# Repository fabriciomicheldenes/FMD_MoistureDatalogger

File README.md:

# 🌱 Datalogger de Umidade do Solo *FMD_Soil Moisture*

## 📘 Visão Geral

 O **FMD_Soil Moisture** é um sistema autônomo para **monitoramento contínuo de umidade e temperatura do solo**, com armazenamento local e conectividade Wi-Fi e Serial-USB.

Projetado para aplicações agrícolas e experimentais, o sistema registra dados ambientais em longo prazo com alta confiabilidade e baixo custo.

O projeto é baseado em um **Arduino Mega 2560**, que coleta leituras de múltiplos sensores capacitivos de umidade do solo **HW-101 HW**, além de um sensor **DHT22** para temperatura e umidade do ar.

Os dados são registrados em **cartão microSD** e podem ser sincronizados via **módulo ESP-01 (ESP8266)** para monitoramento remoto.

## 🧩 Hardware - Arquitetura Geral

### 🔹 Componentes Principais

| Módulo / Componente                                         | Função                            | Interface         | Observações                                                        |
| ----------------------------------------------------------- | --------------------------------- | ----------------- | ------------------------------------------------------------------ |
| **Arduino Mega 2560**                                       | Unidade de controle principal     | –                 | 16 canais analógicos nativos + expansão SPI                        |
| **Sensores de Umidade Capacitivos (HW-101 HW V1.2 / V2.0)** | Medição de umidade do solo        | Analógica (0–5 V) | 16 sensores diretos + 2 via MCP3008                                |
| **MCP3008**                                                 | Conversor A/D externo de 8 canais | SPI               | Expande entradas                                                   |
| **DHT22**                                                   | Temperatura e umidade do ar       | 1 fio (digital)   | Sensor ambiente                                                    |
| **ESP-01 (ESP8266)**                                        | Comunicação Wi-Fi                 | UART              | Upload de dados ou configuração remota                             |
| **RTC DS1307 + Bateria 3 V**                                | Relógio e calendário              | I²C               | Mantém data/hora durante desligamento                              |
| **MicroSD Card (SPI)**                                      | Armazenamento local               | SPI               | Indicadores de status via LEDs                                     |
| **LEDs de Status (3×)**                                     | Indicação do estado do SDCard     | GPIO              | - Sem cartão<br>- Falha no cartão<br>- Cartão OK (pisca ao gravar) |

## ⚙️ Recursos Adicionais (não implementados (no firmware) na versão atual)

| Recurso                | Componente              | Interface | Estado    |
| ---------------------- | ----------------------- | --------- | --------- |
| Memória EEPROM externa | 24C32WP                 | I²C       | Reservado |
| Display LCD 1602       | HD44780 (modo 4 bits)   | GPIO      | Reservado |
| Display 5110           | Nokia 5110              | SPI       | Reservado |
| Teclado                | Teclado matricial 4×4   | GPIO      | Reservado |
| Expansão ADC           | MCP3008 (canais livres) | SPI       | Reservado |

## 🔌 Conectores de Expansão

| Conector                | Interface               | Descrição                                          |
| ----------------------- | ----------------------- | -------------------------------------------------- |
| **Expansão A**          | I²C, 1× I/O, 2× PWM     | Compatível com sensores e atuadores externos       |
| **Expansão B**          | SPI, CS, 1× I/O, 1× PWM | Para módulos SPI adicionais                        |
| **Expansão C**          | SPI, CS, 1× I/O, 1× PWM | Similar à Expansão B                               |
| **Expansão D (Serial)** | TX/RX, 1× I/O, 2× PWM   | Conexão de módulos seriais ou periféricos externos |
| **Planejado**           | RS-232 e RS-485         | UART + controle de hardware                        |

## 🧾 Histórico de Versões do Hardware

| Versão   | Plataforma            | Descrição                                               | Status    |
| -------- | --------------------- | ------------------------------------------------------- | --------- |
| **V0.1** | Proteus (ISIS + ARES) | Primeira versão funcional do circuito e layout          | ✅ Testada |
| **V0.2** | KiCad 8               | Novo layout, roteamento otimizado e serigrafia revisada | 🔄 Atual  |

A **versão V0.1**, desenvolvida no *Proteus (ISIS + ARES)*, foi a primeira versão funcional do hardware, mas apresentava algumas limitações de projeto, como trilhas longas e cruzadas, componentes em ambos os lados e uso reduzido de plano de terra, exigindo pequenas correções com jumpers.

A **versão V0.2**, redesenhada no *KiCad 8*, manteve o mesmo circuito eletrônico, mas trouxe um layout mais maduro e eficiente: todos os componentes estão em um único lado, as trilhas são curtas e bem distribuídas, e há ampla costura de planos de terra em ambas as faces, resultando em **melhor imunidade a ruídos** e maior confiabilidade do sistema.

## 💾 Firmware

O firmware foi desenvolvido em **Arduino C++**, com foco em modularidade e confiabilidade para operação contínua.  
Ele realiza:

- Leitura sequencial dos sensores de umidade e do DHT22  
- Registro no **RTC DS1307** para carimbo de data/hora  
- Armazenamento no **microSD (FAT32)**  
- Indicação visual do status via LEDs  
- Envio de dados via **Wi-Fi (ESP-01)**  

### 🔹 Bibliotecas utilizadas

- `DHT.h` – leitura de temperatura/umidade  
- `Wire.h` – comunicação I²C (RTC e EEPROM)  
- `SPI.h` – comunicação SPI (SD e MCP3008)  
- `SD.h` – gerenciamento do cartão microSD  
- `SoftwareSerial.h` – interface serial com ESP-01  

> 🔗 Detalhes do código e pinagem em [`Firmware/README.md`](Firmware/README.md)

---

## 💻 Software de Visualização

O software de visualização foi desenvolvido em **Python/Qt**, permitindo:

- Leitura direta dos arquivos `.CSV` ou `.TXT` do microSD  
- Exibição de gráficos de tendência (umidade x tempo)  
- Exportação dos dados para análise estatística  
- Modo de operação **offline (SD)** e **online (Wi-Fi)**  

> 🔗 Documentação completa em [`Software/README.md`](Software/README.md)

---

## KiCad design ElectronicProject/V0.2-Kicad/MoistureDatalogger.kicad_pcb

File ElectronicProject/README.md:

# 🌱 Datalogger de Umidade do Solo *FMD_Soil Moisture* – Hardware

## 📘 Visão Geral

 O **FMD_Soil Moisture** é um sistema autônomo para **monitoramento contínuo de umidade e temperatura do solo**, com armazenamento local e conectividade Wi-Fi e Serial-USB.

Projetado para aplicações agrícolas e experimentais, o sistema registra dados ambientais em longo prazo com alta confiabilidade e baixo custo.

O projeto é baseado em um **Arduino Mega 2560**, que coleta leituras de múltiplos sensores capacitivos de umidade do solo **HW-101 HW**, além de um sensor **DHT22** para temperatura e umidade do ar.

Os dados são registrados em **cartão microSD** e podem ser sincronizados via **módulo ESP-01 (ESP8266)** para monitoramento remoto.

## 🧩 Arquitetura Geral

### 🔹 Componentes Principais

| Módulo / Componente                                         | Função                            | Interface         | Observações                                                        |
| ----------------------------------------------------------- | --------------------------------- | ----------------- | ------------------------------------------------------------------ |
| **Arduino Mega 2560**                                       | Unidade de controle principal     | –                 | 16 canais analógicos nativos + expansão SPI                        |
| **Sensores de Umidade Capacitivos (HW-101 HW V1.2 / V2.0)** | Medição de umidade do solo        | Analógica (0–5 V) | 16 sensores diretos + 2 via MCP3008                                |
| **MCP3008**                                                 | Conversor A/D externo de 8 canais | SPI               | Expande entradas                                                   |
| **DHT22**                                                   | Temperatura e umidade do ar       | 1 fio (digital)   | Sensor ambiente                                                    |
| **ESP-01 (ESP8266)**                                        | Comunicação Wi-Fi                 | UART              | Upload de dados ou configuração remota                             |
| **RTC DS1307 + Bateria 3 V**                                | Relógio e calendário              | I²C               | Mantém data/hora durante desligamento                              |
| **MicroSD Card (SPI)**                                      | Armazenamento local               | SPI               | Indicadores de status via LEDs                                     |
| **LEDs de Status (3×)**                                     | Indicação do estado do SDCard     | GPIO              | - Sem cartão<br>- Falha no cartão<br>- Cartão OK (pisca ao gravar) |

## ⚙️ Recursos Adicionais (não implementados (no firmware) na versão atual)

| Recurso                | Componente              | Interface | Estado    |
| ---------------------- | ----------------------- | --------- | --------- |
| Memória EEPROM externa | 24C32WP                 | I²C       | Reservado |
| Display LCD 1602       | HD44780 (modo 4 bits)   | GPIO      | Reservado |
| Display 5110           | Nokia 5110              | SPI       | Reservado |
| Teclado                | Teclado matricial 4×4   | GPIO      | Reservado |
| Expansão ADC           | MCP3008 (canais livres) | SPI       | Reservado |

## 🔌 Conectores de Expansão

| Conector                | Interface               | Descrição                                          |
| ----------------------- | ----------------------- | -------------------------------------------------- |
| **Expansão A**          | I²C, 1× I/O, 2× PWM     | Compatível com sensores e atuadores externos       |
| **Expansão B**          | SPI, CS, 1× I/O, 1× PWM | Para módulos SPI adicionais                        |
| **Expansão C**          | SPI, CS, 1× I/O, 1× PWM | Similar à Expansão B                               |
| **Expansão D (Serial)** | TX/RX, 1× I/O, 2× PWM   | Conexão de módulos seriais ou periféricos externos |
| **Planejado**           | RS-232 e RS-485         | UART + controle de hardware                        |

## 🧾 Histórico de Versões do Hardware

| Versão   | Plataforma            | Descrição                                               | Status    |
| -------- | --------------------- | ------------------------------------------------------- | --------- |
| **V0.1** | Proteus (ISIS + ARES) | Primeira versão funcional do circuito e layout          | ✅ Testada |
| **V0.2** | KiCad 8               | Novo layout, roteamento otimizado e serigrafia revisada | 🔄 Atual  |

As **Figuras 1 e 2** apresentam a **versão V0.1** da placa, elaborada utilizando o *Proteus* (ISIS + ARES).  
Embora plenamente funcional, essa versão apresentou algumas limitações construtivas, como **trilhas incompletas que precisaram ser interligadas externamente por jumpers**, um **layout ainda imaturo** com **componentes montados em ambos os lados da placa** e **trilhas longas que se cruzam**, resultando em **pouca área disponível para o plano de terra**.  
Esses aspectos podem ser observados nas **Figuras 3 e 4**, que mostram os lados **superior** e **inferior** da placa.

<figure>
  
  <figcaption align="center"><b>Figura 1</b>: Placa V0.1 vista de cima.  <b> Figura 2</b>: – Placa V0.1 vista de baixo.</figcaption>
</figure>

<figure>
  
  <figcaption align="center"><b>Figura 3</b>: Placa V0.1 Top layer.  <b> Figura 4</b>: – Placa V0.1 Bottom layer.</figcaption>
</figure>>

A **versão V0.2**, desenvolvida no **KiCad**, manteve o mesmo circuito eletrônico da versão anterior, porém recebeu um **layout totalmente refeito**, com foco em otimização e robustez.  
Como ilustrado nas **Figuras 5 e 6**, o novo modelo 3D demonstra um **posicionamento mais racional dos componentes**, concentrados **em um único lado da placa**, com **trilhas mais curtas e diretas** e **ampla área para planos de terra em ambas as faces**.  
As **Figuras 7 e 8** evidenciam também a **costura entre planos de terra**, que contribui para **melhorar a imunidade a ruídos** e **reduzir interferências eletromagnéticas (EMI)**, tornando o hardware mais confiável para uso em ambientes agrícolas sujeitos a variações de umidade e ruído elétrico.

<figure>
  
  <figcaption align="center"><b>Figura 5</b>: Placa V0.2 vista de cima, modelo 3D.  <b> Figura 6</b>: – Placa V0.2 vista de baixo, modelo 3D.</figcaption>
</figure>

<figure>
  
  <figcaption align="center"><b>Figura 7</b>: Placa V0.2 Top layer.  <b> Figura 8</b>: – Placa V0.2 Bottom layer.</figcaption>
</figure>>

## 🧮 Especificações Técnicas

- **Alimentação:** 7 – 12 V DC
- **Consumo típico:** ~200 mA (sem Wi-Fi ativo)
- **Número total de canais de umidade:** 18
- **Resolução ADC (interna):** 10 bits
- **Resolução ADC (externa):** 10 bits (MCP3008)
- **Período de amostragem:** configurável (ex.: 5 s a 10 min)
- **Armazenamento:** microSD FAT32 (até 32 GB)
- **Conectividade:** Wi-Fi (ESP-01), Serial USB

## 🧰 Próximas Melhorias

- Implementação do barramento **RS-485** para rede de sensores.
- Inclusão de **display LCD/Nokia** para feedback local.
- Sistema de **menus via teclado matricial**.
- Adição de **EEPROM 24C32WP** para parâmetros persistentes.

## 📁 Estrutura de Pastas (Hardware)

## 📜 Licença

Este projeto é distribuído sob a licença **MIT**, permitindo uso, modificação e distribuição com atribuição ao autor.

---

**Autor:** Fabrício Michel Denes  
**Repositório:** [github.com/fabriciomicheldenes/FMD_MoistureDatalogger](https://github.com/fabriciomicheldenes/FMD_MoistureDatalogger)

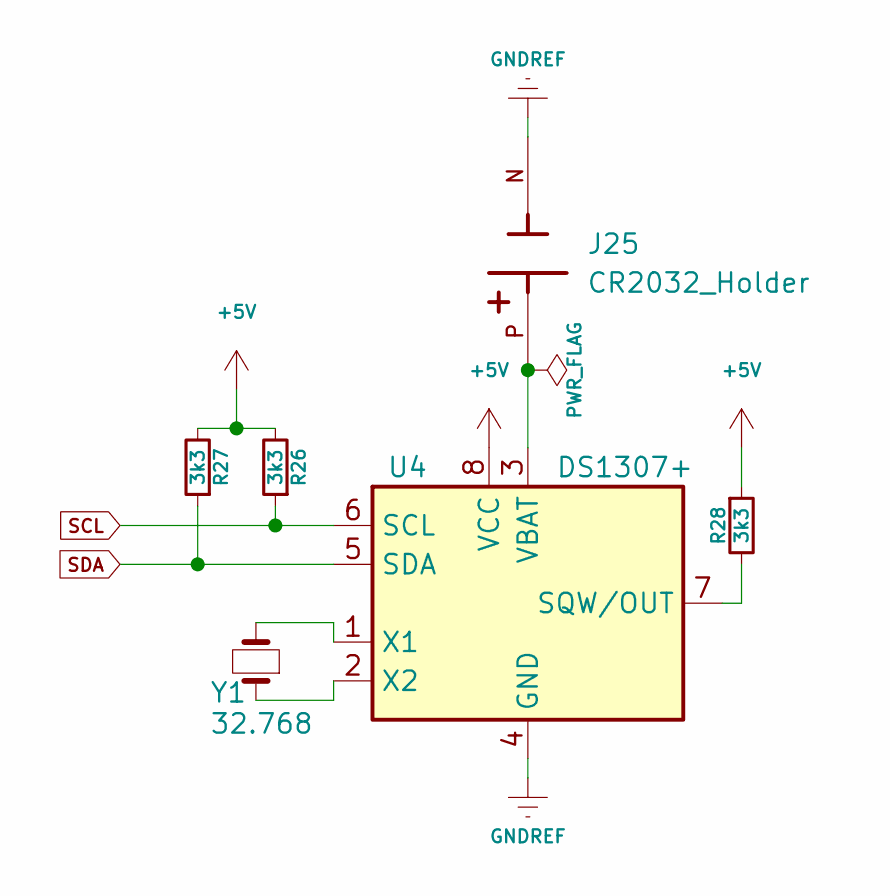
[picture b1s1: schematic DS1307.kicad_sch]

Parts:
J25: CR2032_Holder; HARWIN_S8421-45R
R26, R27, R28: 3k3; R_0805_2012Metric
U4: DS1307+; SOIC-8_3.9x4.9mm_P1.27mm
Y1: 32.768; Crystal_DS26_D2.0mm_L6.0mm_Vertical

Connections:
+5V: R26.2, R27.2, R28.1, U4.8 (VCC); also elsewhere on the board
GNDREF: J25.N, U4.4 (GND); also elsewhere on the board
unnamed: R28.2, U4.7 (SQW/OUT)
unnamed: J25.P, U4.3 (VBAT)
unnamed: U4.1 (X1), Y1.2
unnamed: U4.2 (X2), Y1.1
SCL: R26.1, U4.6 (SCL); also elsewhere on the board
SDA: R27.1, U4.5 (SDA); also elsewhere on the board

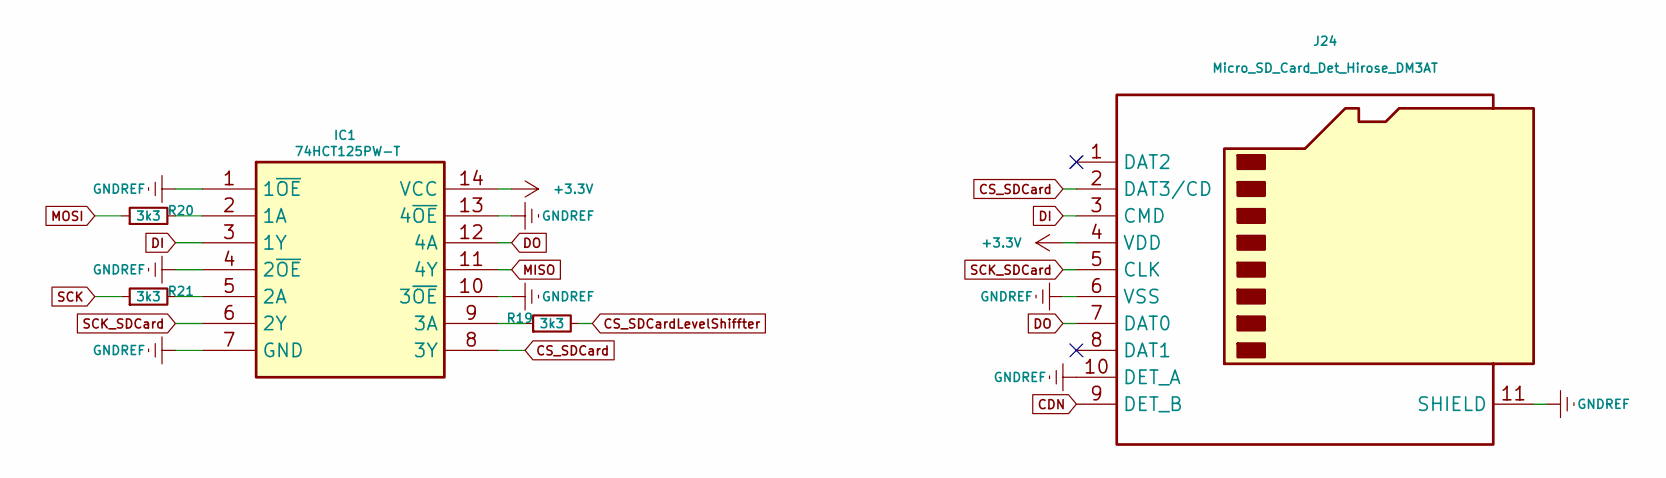
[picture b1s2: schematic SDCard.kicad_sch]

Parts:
IC1: 74HCT125PW-T; SOIC-14_3.9x8.7mm_P1.27mm; Manufacturer_Part_Number 74HCT125PW-T
J24: Micro_SD_Card_Det_Hirose_DM3AT; microSD_HC_Hirose_DM3AT-SF-PEJM5
R19, R20, R21: 3k3; R_0805_2012Metric

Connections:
+3.3V: IC1.14 (VCC), J24.4 (VDD); also elsewhere on the board
CDN: J24.9 (DET_B); also elsewhere on the board
CS_SDCard: IC1.8 (3Y), J24.2 (DAT3/CD)
CS_SDCardLevelShiffter: R19.2; also elsewhere on the board
DI: IC1.3 (1Y), J24.3 (CMD)
DO: IC1.12 (4A), J24.7 (DAT0)
GNDREF: IC1.1 (1~OE), IC1.4 (2~OE), IC1.7 (GND), IC1.10 (3~OE), IC1.13 (4~OE), J24.6 (VSS), J24.10 (DET_A), J24.11 (SHIELD); also elsewhere on the board
MISO: IC1.11 (4Y); also elsewhere on the board
MOSI: R20.1; also elsewhere on the board
unnamed: IC1.2 (1A), R20.2
unnamed: IC1.5 (2A), R21.2
unnamed: IC1.9 (3A), R19.1
SCK: R21.1; also elsewhere on the board
SCK_SDCard: IC1.6 (2Y), J24.5 (CLK)

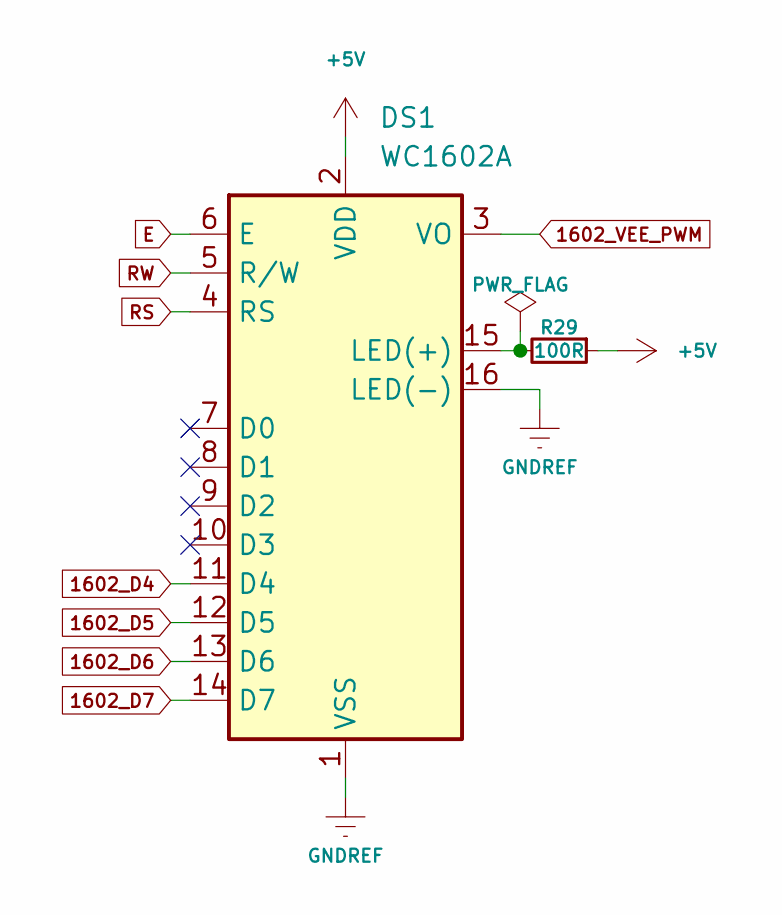
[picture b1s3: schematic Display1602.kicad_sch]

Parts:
DS1: WC1602A; JST_XH_B16B-XH-A_1x16_P2.50mm_Vertical
R29: 100R; R_0805_2012Metric

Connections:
1602_D4: DS1.11 (D4); also elsewhere on the board
1602_D5: DS1.12 (D5); also elsewhere on the board
1602_D6: DS1.13 (D6); also elsewhere on the board
1602_D7: DS1.14 (D7); also elsewhere on the board
1602_VEE_PWM: DS1.3 (VO); also elsewhere on the board
+5V: DS1.2 (VDD), R29.1; also elsewhere on the board
E: DS1.6 (E); also elsewhere on the board
GNDREF: DS1.1 (VSS), DS1.16 (LED(-)); also elsewhere on the board
unnamed: DS1.15 (LED(+)), R29.2
RS: DS1.4 (RS); also elsewhere on the board
RW: DS1.5 (R/W); also elsewhere on the board

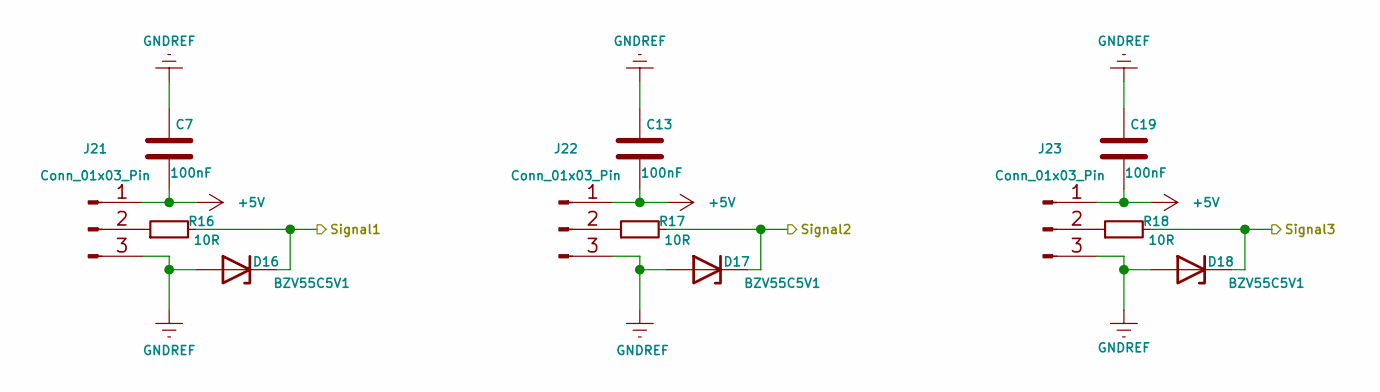
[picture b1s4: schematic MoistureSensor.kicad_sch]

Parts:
C7, C13, C19: 100nF; C_0805_2012Metric
D16, D17, D18: BZV55C5V1; D_DO-15_P10.16mm_Horizontal
J21, J22, J23: Conn_01x03_Pin; JST_XH_B3B-XH-AM_1x03_P2.50mm_Vertical
R16, R17, R18: 10R; R_0805_2012Metric

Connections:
+5V: C7.2, C13.2, C19.2, J21.1, J22.1, J23.1; also elsewhere on the board
/Microcontroller2560/A0: D16.1 (K), R16.2; also elsewhere on the board
/Microcontroller2560/A1: D17.1 (K), R17.2; also elsewhere on the board
/Microcontroller2560/A2: D18.1 (K), R18.2; also elsewhere on the board
GNDREF: C7.1, C13.1, C19.1, D16.2 (A), D17.2 (A), D18.2 (A), J21.3, J22.3, J23.3; also elsewhere on the board
unnamed: J21.2, R16.1
unnamed: J22.2, R17.1
unnamed: J23.2, R18.1

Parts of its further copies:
C8, C9, C10, C11, C12, C14, C15, C16, C17, C18, C20, C21, C22, C23, C24: 100nF; C_0805_2012Metric
D1, D2, D3, D4, D5, D6, D7, D8, D9, D10, D11, D12, D13, D14, D15: BZV55C5V1; D_DO-15_P10.16mm_Horizontal
J5, J6, J7, J8, J9, J10, J11, J12, J13, J14, J15, J16, J17, J18, J19: Conn_01x03_Pin; JST_XH_B3B-XH-AM_1x03_P2.50mm_Vertical
R1, R2, R3, R4, R5, R6, R7, R8, R9, R10, R11, R12, R13, R14, R15: 10R; R_0805_2012Metric

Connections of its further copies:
+5V: C8.2, C9.2, C10.2, C11.2, C12.2, C14.2, C15.2, C16.2, C17.2, C18.2, C20.2, C21.2, C22.2, C23.2, C24.2, J5.1, J6.1, J7.1, J8.1, J9.1, J10.1, J11.1, J12.1, J13.1, J14.1, J15.1, J16.1, J17.1, J18.1, J19.1; also elsewhere on the board
/MCP3008/A16: D14.1 (K), R14.2; also elsewhere on the board
/MCP3008/A17: D15.1 (K), R15.2; also elsewhere on the board
/Microcontroller2560/A3: D1.1 (K), R1.2; also elsewhere on the board
/Microcontroller2560/A4: D2.1 (K), R2.2; also elsewhere on the board
/Microcontroller2560/A5: D3.1 (K), R3.2; also elsewhere on the board
/Microcontroller2560/A6: D4.1 (K), R4.2; also elsewhere on the board
/Microcontroller2560/A7: D5.1 (K), R5.2; also elsewhere on the board
/Microcontroller2560/A8: D6.1 (K), R6.2; also elsewhere on the board
/Microcontroller2560/A9: D7.1 (K), R7.2; also elsewhere on the board
/Microcontroller2560/A10: D8.1 (K), R8.2; also elsewhere on the board
/Microcontroller2560/A11: D9.1 (K), R9.2; also elsewhere on the board
/Microcontroller2560/A12: D10.1 (K), R10.2; also elsewhere on the board
/Microcontroller2560/A13: D11.1 (K), R11.2; also elsewhere on the board
/Microcontroller2560/A14: D12.1 (K), R12.2; also elsewhere on the board
/Microcontroller2560/A15: D13.1 (K), R13.2; also elsewhere on the board
GNDREF: C8.1, C9.1, C10.1, C11.1, C12.1, C14.1, C15.1, C16.1, C17.1, C18.1, C20.1, C21.1, C22.1, C23.1, C24.1, D1.2 (A), D2.2 (A), D3.2 (A), D4.2 (A), D5.2 (A), D6.2 (A), D7.2 (A), D8.2 (A), D9.2 (A), D10.2 (A), D11.2 (A), D12.2 (A), D13.2 (A), D14.2 (A), D15.2 (A), J5.3, J6.3, J7.3, J8.3, J9.3, J10.3, J11.3, J12.3, J13.3, J14.3, J15.3, J16.3, J17.3, J18.3, J19.3; also elsewhere on the board
unnamed: J5.2, R1.1
unnamed: J6.2, R2.1
unnamed: J7.2, R3.1
unnamed: J8.2, R4.1
unnamed: J9.2, R5.1
unnamed: J10.2, R6.1
unnamed: J11.2, R7.1
unnamed: J12.2, R8.1
unnamed: J13.2, R9.1
unnamed: J14.2, R10.1
unnamed: J15.2, R11.1
unnamed: J16.2, R12.1
unnamed: J17.2, R13.1
unnamed: J18.2, R14.1
unnamed: J19.2, R15.1

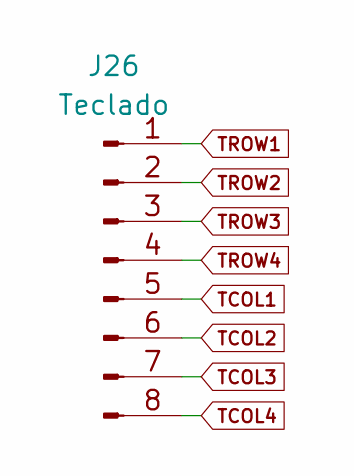
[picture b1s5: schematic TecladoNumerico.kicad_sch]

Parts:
J26: Teclado; JST_XH_B8B-XH-A_1x08_P2.50mm_Vertical

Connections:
TCOL1: J26.5; also elsewhere on the board
TCOL2: J26.6; also elsewhere on the board
TCOL3: J26.7; also elsewhere on the board
TCOL4: J26.8; also elsewhere on the board
TROW1: J26.1; also elsewhere on the board
TROW2: J26.2; also elsewhere on the board
TROW3: J26.3; also elsewhere on the board
TROW4: J26.4; also elsewhere on the board

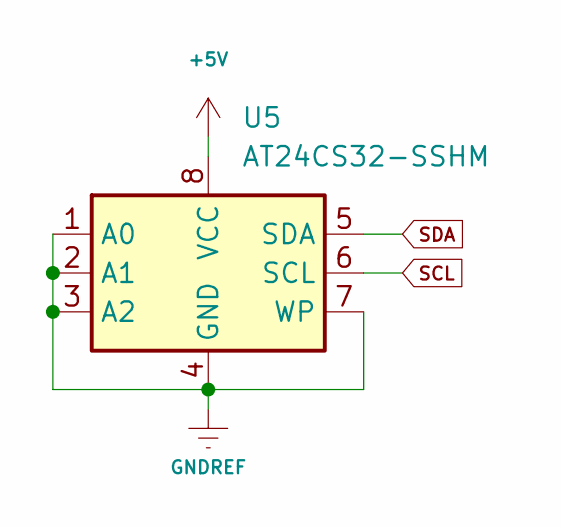
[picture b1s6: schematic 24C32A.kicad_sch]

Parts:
U5: AT24CS32-SSHM; SOIC-8_3.9x4.9mm_P1.27mm

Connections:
+5V: U5.8 (VCC); also elsewhere on the board
GNDREF: U5.1 (A0), U5.2 (A1), U5.3 (A2), U5.4 (GND), U5.7 (WP); also elsewhere on the board
SCL: U5.6 (SCL); also elsewhere on the board
SDA: U5.5 (SDA); also elsewhere on the board

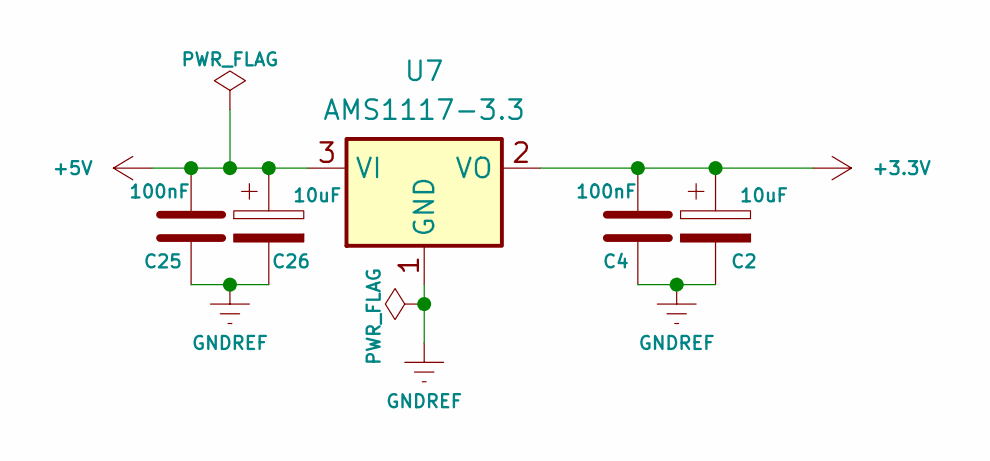
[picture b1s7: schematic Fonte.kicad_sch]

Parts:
C2: 10uF; C_0805_2012Metric
C4, C25: 100nF; C_0805_2012Metric
C26: 10uF; CP_Elec_5x5.8
U7: AMS1117-3.3; SOT-223-3_TabPin2

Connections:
+3.3V: C2.1, C4.2, U7.2 (VO); also elsewhere on the board
+5V: C25.2, C26.1, U7.3 (VI); also elsewhere on the board
GNDREF: C2.2, C4.1, C25.1, C26.2, U7.1 (GND); also elsewhere on the board

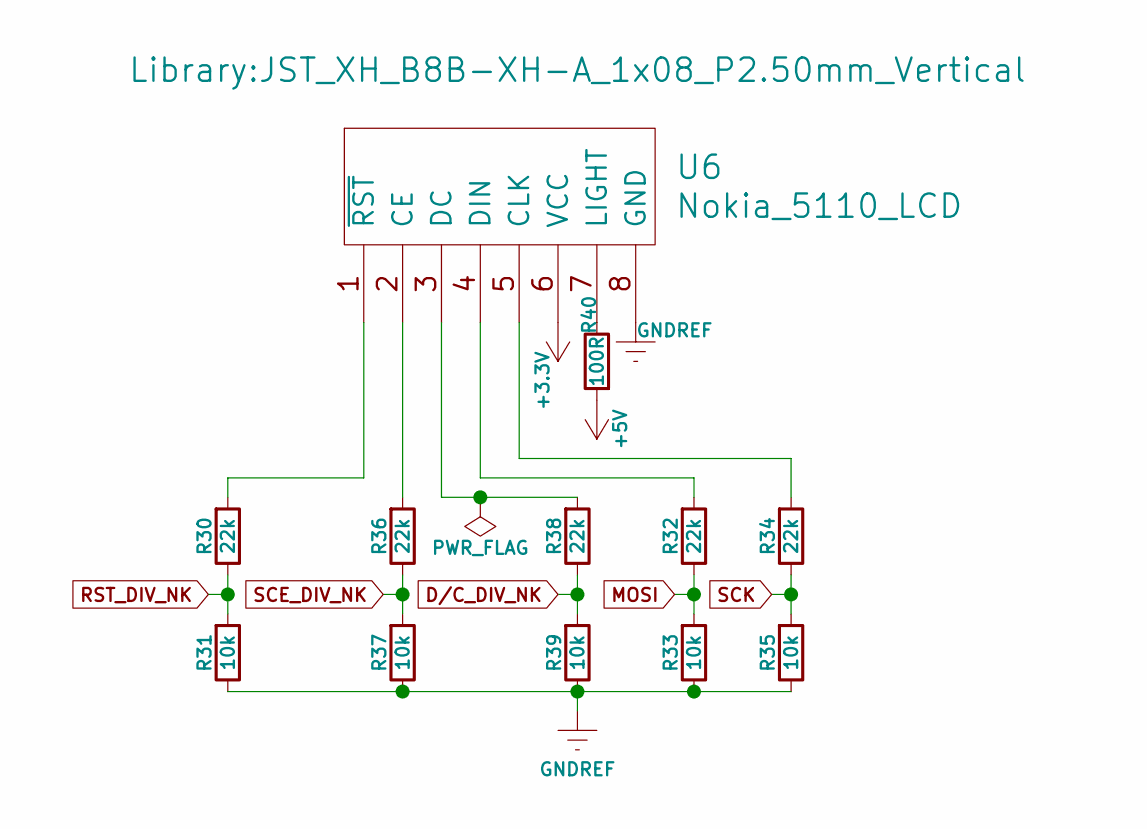
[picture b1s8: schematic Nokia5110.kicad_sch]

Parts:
R30, R32, R34, R36, R38: 22k; R_0805_2012Metric
R31, R33, R35, R37, R39: 10k; R_0805_2012Metric
R40: 100R; R_0805_2012Metric
U6: Nokia_5110_LCD; JST_XH_B8B-XH-A_1x08_P2.50mm_Vertical

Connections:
+3.3V: U6.6 (VCC); also elsewhere on the board
+5V: R40.1; also elsewhere on the board
D/C_DIV_NK: R38.2, R39.1; also elsewhere on the board
GNDREF: R31.2, R33.2, R35.2, R37.2, R39.2, U6.8 (GND); also elsewhere on the board
MOSI: R32.2, R33.1; also elsewhere on the board
unnamed: R36.1, U6.2 (CE)
unnamed: R34.1, U6.5 (CLK)
unnamed: R38.1, U6.3 (DC)
unnamed: R32.1, U6.4 (DIN)
unnamed: R40.2, U6.7 (LIGHT)
unnamed: R30.1, U6.1 (~RST)
RST_DIV_NK: R30.2, R31.1; also elsewhere on the board
SCE_DIV_NK: R36.2, R37.1; also elsewhere on the board
SCK: R34.2, R35.1; also elsewhere on the board

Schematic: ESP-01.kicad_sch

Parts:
R22, R25: 2k2; R_0805_2012Metric
R23, R24: 1k; R_0805_2012Metric
U2: ESP-01; MODULE_ESP-01; PARTREV 1.0

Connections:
+3.3V: U2.5 (VCC); also elsewhere on the board
CS_ESP: R25.2; also elsewhere on the board
ESP_~RST: U2.6 (~RST); also elsewhere on the board
GNDREF: R23.1, R24.1, U2.1 (GND); also elsewhere on the board
unnamed: R24.2, R25.1, U2.7 (CH_PD)
unnamed: R22.1, R23.2, U2.4 (RXD)
RX_ARD: U2.8 (TXD); also elsewhere on the board
TX_ARD: R22.2; also elsewhere on the board

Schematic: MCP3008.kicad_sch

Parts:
C5: 100nF; C_0805_2012Metric
C6: 10uF; C_0805_2012Metric
J20: ANALOG_EXP; JST_XH_B8B-XH-A_1x08_P2.50mm_Vertical
U1: MCP3008; SOIC-16_3.9x9.9mm_P1.27mm

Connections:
+5V: C5.2, C6.1, J20.7, U1.15 (Vref), U1.16 (Vdd); also elsewhere on the board
/MCP3008/A16: U1.1 (CH0); also elsewhere on the board
/MCP3008/A17: U1.2 (CH1); also elsewhere on the board
CS_MCP3008: U1.10 (~CS/SHDN); also elsewhere on the board
GNDREF: C5.1, C6.2, J20.8, U1.9 (DGND), U1.14 (AGND); also elsewhere on the board
MISO: U1.12 (Dout); also elsewhere on the board
MOSI: U1.11 (Din); also elsewhere on the board
unnamed: J20.1, U1.3 (CH2)
unnamed: J20.2, U1.4 (CH3)
unnamed: J20.3, U1.5 (CH4)
unnamed: J20.4, U1.6 (CH5)
unnamed: J20.5, U1.7 (CH6)
unnamed: J20.6, U1.8 (CH7)
SCK: U1.13 (CLK); also elsewhere on the board

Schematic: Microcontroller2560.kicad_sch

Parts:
A1: Arduino_Mega2560_R3_Shield
C1: 10uF; CP_Elec_5x5.8
C3: 100nF; C_0805_2012Metric
D19: LED_RED; LED_D3.0mm
D20: LED_YELLOW; LED_D3.0mm
D21: LED_GREEN; LED_D3.0mm
J1: EXP_SPI_01; JST_XH_B8B-XH-A_1x08_P2.50mm_Vertical
J2: EXP_I2C; JST_XH_B8B-XH-A_1x08_P2.50mm_Vertical
J3: EXP_UART; JST_XH_B8B-XH-A_1x08_P2.50mm_Vertical
J4: EXP_SPI_02; JST_XH_B8B-XH-A_1x08_P2.50mm_Vertical
R41, R42, R43: 100R; R_0805_2012Metric

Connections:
1602_D4: A1.D28; also elsewhere on the board
1602_D5: A1.D29; also elsewhere on the board
1602_D6: A1.D30; also elsewhere on the board
1602_D7: A1.D31; also elsewhere on the board
1602_VEE_PWM: A1.D4; also elsewhere on the board
+3.3V: J1.8, J2.8, J3.8, J4.8; also elsewhere on the board
+5V: A1.5V1 (5V), A1.5V3 (5V), A1.5V4 (5V), C1.1, C3.2, J1.2, J2.2, J3.2, J4.2; also elsewhere on the board
/Microcontroller2560/A0: A1.A0; also elsewhere on the board
/Microcontroller2560/A1: A1.A1; also elsewhere on the board
/Microcontroller2560/A2: A1.A2; also elsewhere on the board
/Microcontroller2560/A3: A1.A3; also elsewhere on the board
/Microcontroller2560/A4: A1.A4; also elsewhere on the board
/Microcontroller2560/A5: A1.A5; also elsewhere on the board
/Microcontroller2560/A6: A1.A6; also elsewhere on the board
/Microcontroller2560/A7: A1.A7; also elsewhere on the board
/Microcontroller2560/A8: A1.A8; also elsewhere on the board
/Microcontroller2560/A9: A1.A9; also elsewhere on the board
/Microcontroller2560/A10: A1.A10; also elsewhere on the board
/Microcontroller2560/A11: A1.A11; also elsewhere on the board
/Microcontroller2560/A12: A1.A12; also elsewhere on the board
/Microcontroller2560/A13: A1.A13; also elsewhere on the board
/Microcontroller2560/A14: A1.A14; also elsewhere on the board
/Microcontroller2560/A15: A1.A15; also elsewhere on the board
CDN: A1.D49; also elsewhere on the board
CS_ESP: A1.D13; also elsewhere on the board
CS_MCP3008: A1.D48, A1.D53 (D53_CS); also elsewhere on the board
CS_SDCardLevelShiffter: A1.D44; also elsewhere on the board
DHT_DATA: A1.D6; also elsewhere on the board
D/C_DIV_NK: A1.D24; also elsewhere on the board
E: A1.D27; also elsewhere on the board
ESP_~RST: A1.D5; also elsewhere on the board
EXP_D0: A1.D40, J1.6
EXP_D1: A1.D41, J4.6
EXP_D2: A1.D42, J2.5
EXP_D3: A1.D43, J3.5
EXP_PWM_01: A1.D12, J1.7
EXP_PWM_02: A1.D11, J4.7
EXP_PWM_03: A1.D10, J2.6
EXP_PWM_04: A1.D9, J2.7
EXP_PWM_05: A1.D8, J3.6
EXP_PWM_06: A1.D7, J3.7
GNDREF: A1.GND1 (GND), A1.GND2 (GND), A1.GND3 (GND), A1.GND5 (GND), A1.GND6 (GND), C1.2, C3.1, D19.1 (K), D20.1 (K), D21.1 (K), J1.1, J2.1, J3.1, J4.1; also elsewhere on the board
MISO: A1.D50 (D50_MISO), J1.4, J4.4; also elsewhere on the board
MOSI: A1.D51 (D51_MOSI), J1.3, J4.5; also elsewhere on the board
unnamed: D19.2 (A), R41.2
unnamed: D20.2 (A), R42.2
unnamed: D21.2 (A), R43.2
RS: A1.D25; also elsewhere on the board
RST_DIV_NK: A1.D22; also elsewhere on the board
RW: A1.D26; also elsewhere on the board
RX2_ARD: A1.D17 (D17/RX2), J3.4
RX_ARD: A1.D19 (D19/RX1); also elsewhere on the board
SCE_DIV_NK: A1.D23; also elsewhere on the board
SCK: A1.D52 (D52_SCK), J1.5, J4.3; also elsewhere on the board
SCL: A1.SCL, J2.3; also elsewhere on the board
SDA: A1.SDA, J2.4; also elsewhere on the board
SDCARD_FAIL: A1.D45, R41.1
SDCARD_NONE: A1.D46, R42.1
SDCARD_OK: A1.D47, R43.1
TCOL1: A1.D36; also elsewhere on the board
TCOL2: A1.D37; also elsewhere on the board
TCOL3: A1.D38; also elsewhere on the board
TCOL4: A1.D39; also elsewhere on the board
TROW1: A1.D32; also elsewhere on the board
TROW2: A1.D33; also elsewhere on the board
TROW3: A1.D34; also elsewhere on the board
TROW4: A1.D35; also elsewhere on the board
TX2_ARD: A1.D16 (D16/TX2), J3.3
TX_ARD: A1.D18 (D18/TX1); also elsewhere on the board

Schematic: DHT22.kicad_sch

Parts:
U3: DHT22; XDCR_DHT22

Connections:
+5V: U3.1 (VDD); also elsewhere on the board
DHT_DATA: U3.2 (DATA); also elsewhere on the board
GNDREF: U3.4 (GND); also elsewhere on the board

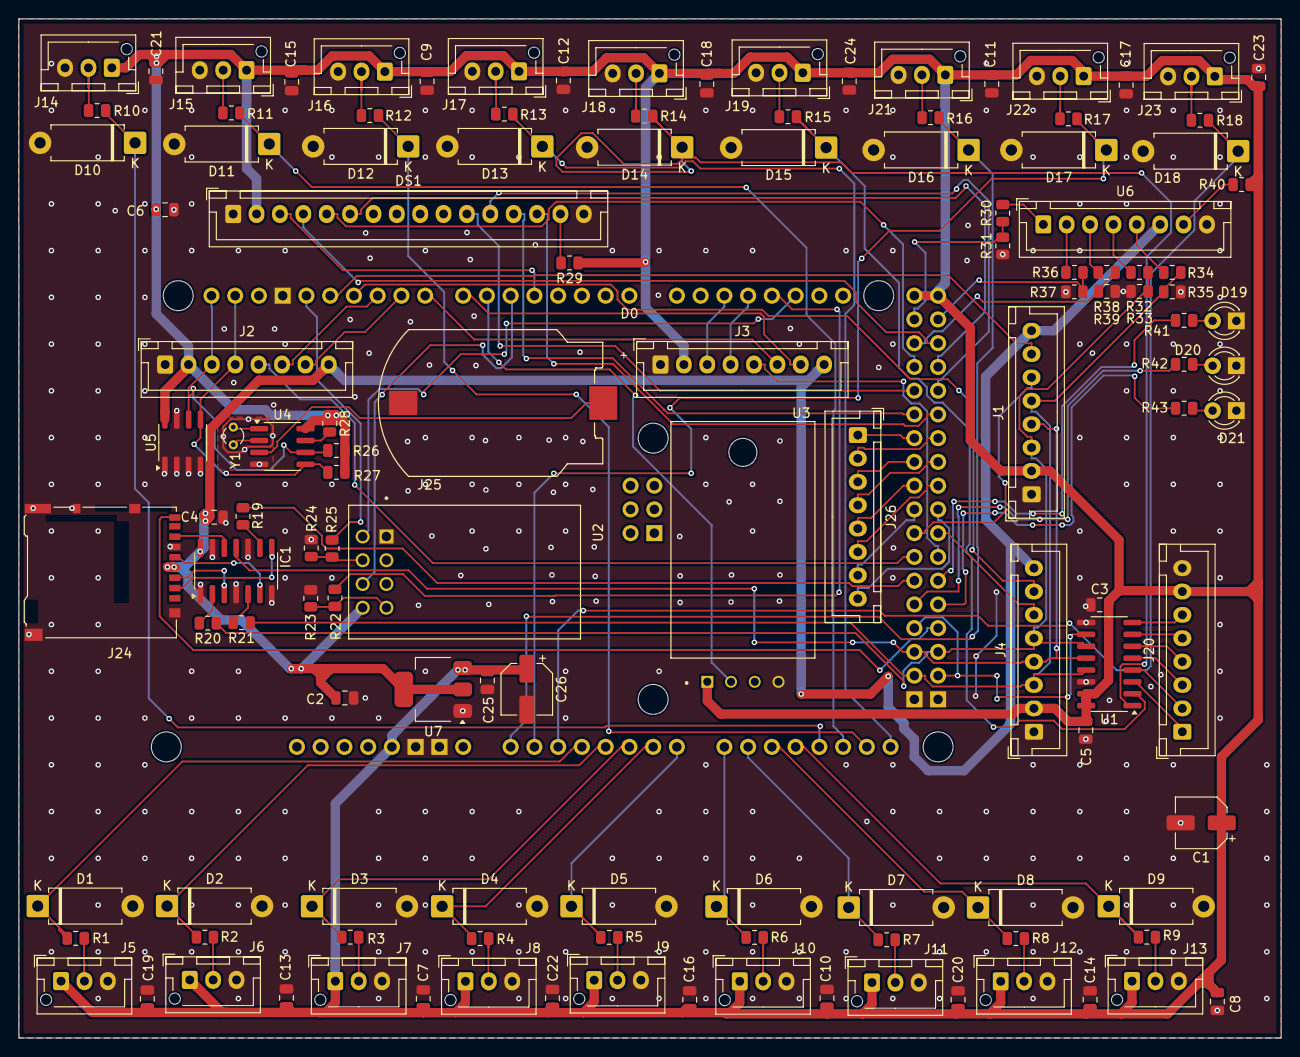
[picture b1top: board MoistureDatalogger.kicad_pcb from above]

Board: 2 copper layers, 135.0 x 109.0 mm, 127 parts (0 on the bottom side), 115 nets.

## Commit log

2025-11-09 feat(base): Base do projeto, com DHT, RTC e ADC nativos do ATmega2560
2025-11-09 feat(base): Versão inicial com DHT, RTC e ADC nativos do ATmega2560
2025-11-09 Adiciona README.md para o projeto eletrônico
2025-11-09 Remove o diretorio Firmware/lib/ erroneamente incluido em .gitignore
2025-11-09 Revert "Para correção da mensagem de commit"
    Reverção de commit para correção da mensagem de commit
    "Remove o diretorio Firmware/lib/ erroneamente incluido em .gitignore"
    This reverts commit 67b3b7ca788ff74ad37eca1d53646c23d2f6961b.
2025-11-09 Restaura o diretorio lib, erroneamente ignorado
2025-11-10 feat(drivers): adiciona suporte ao ADC MCP3008 como sensores individuais
    - Implementa as classes `Mcp3008Driver` e `Mcp3008ChannelSensor`, integradas à interface ISensor.
    - Cada canal do MCP3008 é tratado como um sensor independente (CH0–CH7).
    - Adiciona construtor padrão para permitir inicialização estática de arrays de sensores.
    - Integra os sensores MCP3008 ao DeviceManager, permitindo registro automático e leitura unificada.
    - Atualiza SystemMediator::generateSaveLine() para incluir canais do MCP (17–18) no log serial.
    - Padroniza a coleta e resposta dos sensores ADC nativos e externos (ATmega2560 + MCP3008).
2025-11-11 feat(core): adiciona arquitetura de serviços e integração do SDCard via ISystemService
    - Cria a nova interface ISystemService para gerenciar periféricos de sistema (SDCard, WiFi, etc.)
    - Refatora o SDCardRWController para herdar de ISystemService e retornar status de gravação (SD=OK / SD=ERR)
    - Adiciona suporte a registro e recuperação de serviços no DeviceManager (services[])
    - Atualiza SystemMediator::generateSaveLine() para incluir o resultado da escrita no SDCard
    - Mantém compatibilidade total com a arquitetura baseada em ISensor e SystemMediator
    - Prepara a base para integração futura de novos serviços (WiFi, NTP, Logger)
2025-11-11 feat(sdcard): adiciona controle completo de LED e verificação dinâmica de inserção/remoção do cartão
    - Implementa controle de presença e reinicialização automática do cartão SD
    - Adiciona lógica não bloqueante de piscar LED verde via Timer2 (6 Hz, 50% duty)
    - Atualiza SDCardRWController::updateSDCard() para executar continuamente, mesmo sem cartão inserido
    - Implementa controle visual completo:
    🔴 Vermelho → cartão ausente
    🟡 Amarelo → falha de leitura/gravação
2025-11-13 feat(gui): primeira versão funcional do TerraMoistLogger
    Esta é a primeira versão totalmente funcional da interface gráfica
    do TerraMoistLogger, projetada para monitorar múltiplos dispositivos
    TerraMoistSense (4 unidades / 72 sensores capacitivos).
    Principais funcionalidades implementadas:
    - Leitura serial em tempo real via QSerialPort
    - Detecção automática de conexão/desconexão de dispositivos
2025-11-13 Create README.md for TerraMoistLogger
    Add detailed README for TerraMoistLogger project
